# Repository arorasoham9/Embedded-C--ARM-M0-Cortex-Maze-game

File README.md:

# MazeGame

Links to Parts:
Adafruit LIS3DH Triple-Axis Accelerometer (+-2g/4g/8g/16g) : ID 2809 : $4.95 : Adafruit Industries, Unique & fun DIY electronics and kits
Mini Metal Speaker w/ Wires - 8 ohm 0.5W : ID 1890 : $1.95 : Adafruit Industries, Unique & fun DIY electronics and kits

What kinds of internal peripherals will you use? (at least four)
SPI (Screen), I2C (Accelerometer), Timer (Game time), DAC (Game music), GPIO (Buttons)

What kinds of external interface formats will you use? (at least two)
SPI, I2C, GPIO, Analog

Briefly, what are you making and what are you making it out of?
We are going to make a handheld maze game where you control the ball’s movement by rotating the device relative to gravity. The game will be displayed on the MSP2202 TFT LCD Display and angular position will be provided by an LIS3DH triple-axis accelerometer. Tetris music will be played with the MIDI interpreter used in lab via a M2850-8B-0L03R speaker powered by an LM386 audio amplifier. The LM386 is designed for low voltage consumer applications and is adequately powered by a 5 volt supply. The 24AA32AF EEPROM will save the high score even after the device is shut down and restarted. Five tactile push buttons (up/down/left/right/select) will allow the user to navigate any necessary prompts and menus.

Mazes will be dynamically generated. As mazes are completed, they will increase in size and number of rotations required to solve them. A reasonable minimum/maximum rotation limit will be put in place for each size of maze generated.

Briefly, how will you demonstrate it?
We will have the TA play the game. Each maze must be completed within a time limit or the speaker will buzz. The score achieved and the all-time high score will be displayed. The player will be given the choice to start a new game.

Briefly, how will we define the criteria for a successful project? (If your demonstration does not meet these criteria, your score will be negatively affected.)
The rotation based control should track the device’s position accurately and be free of noise/glitches. The game should be able to be played and completed by any adult with no instructions given (any instructions should be easily accessible within the device itself). The maze levels should gradually increase in size as each subsequent maze is completed. The maze size will level off at a point before the maze paths become hard to discern (however we expect people to lose or quit before this point is reached). The player’s score should be a summation of the time left on the countdown for each maze successfully completed. For example, if a certain level has a time limit of 45 seconds, and the player completes the maze in 30 seconds, 15 points will be added to the player’s total score. The high score should be saved and able to be recalled even after the device is shutdown and powered back on. Music should be clearly audible and free of noise.

#CONCLUSION

What did you build? 	
What components (including model numbers) did you use? 	
What challenges did you face, and how did you overcome them? 	
What do you recommend to anyone doing the same thing or using the same components in the future?

We built a maze game that was controlled by rotation of the board. The maze was dynamically generated and increased in size when each level was passed. Players had a set amount of time, which increased as the game continued, to solve each level. Time remaining and current score were displayed on the maze screen. Level score was equal to the amount of time remaining to complete the maze. Menus at start, next level, and end of game were navigated using push buttons and GPIO. After the level or game ended, score was displayed and the player could choose to continue/quit or start a new game. Navigation within the maze was controlled by an accelerometer that interfaced with I2C. EEPROM was used with I2C to save the high score when the game was reset or power was turned off and on. Tetris music played during gameplay and was set up with a MIDI interpreter and DAC output.
The game was displayed on the MSP2202 TFT LCD Display and angular position was provided by an LIS3DH triple-axis accelerometer. 24AA32AF EEPROM allowed our team to save the high score after power cycles. An LM386 amplifier drove a small 0.5 watt M2850-8B-0L03R speaker. Generic 6mm buttons provided the user-input, and LM1117 regulators allowed the team to power the components at their respective voltages.
One major issue that we encountered was related to the randomness of the maze that we were generating. When we initially wrote the maze program we used time.h to seed the random number generator. However, we learned that time.h cannot be used in our microcontroller. After this, we followed the directions on the references site about seeding random with a timer. Our first attempt at this failed and the mazes were still not random. We realized that this was due to the fact that we were calling srand(TIM2->CNT) at the same time each time the game started. In order to fix this we waited for a button to be pressed before we seeded srand, to ensure a different seed each time. 

We also struggled to correctly display colors. We used GIMP to generate the ball, and its output was not displaying colors correctly. We got around this by copying the number of the color we wanted into the array manually. However, the color was lime green against a white background, and the lack of contrast made the ball difficult to view if the player held the maze screen far away.

One final issue we encountered involved music. We used a weak 0.5 W speaker connected to a LM386 amplifier, and getting output at a reasonable volume was difficult. We needed overly complex circuitry to get volume where you didn’t need to place your ear near the speaker to hear. We also struggled with enabling and disabling the music at correct times in the code. When music was stopped and restarted, there was a remaining contribution that interfered with the sound. To fix this, we disabled the timer and set the voices array values to zero before restarting the music. We also did not correctly set the interrupt priority for the music, and the sound clicked as a result. We did not realize this because of the low output of the speaker, but it became clear during the demonstration when we hooked up the output to the lab speakers. If we had tested with the lab speaker, we would likely have been able to fix this issue.

I would recommend a similar project to teams in the future. We ran into many challenges arriving at our final design, however all problems were manageable with proper time management and teamwork. Every component worked well with the exception of the LM386 audio amplifier. We found the LM386 to be very temperamental and prone to noise on our breadboard, and the suggested schematics in the datasheet had to be modified to attain usable results in our case. A small issue we had with the LIS3DH accelerometer was that the datasheet I2C section indicated that a repeated start bit must be sent when the master is receiving data from the accelerometer. We couldn’t figure out how to do this, but after research we found that the repeated start wasn’t necessary- sending a stop bit first followed by a start bit also functioned properly. Once this was figured out the accelerometer worked flawlessly.

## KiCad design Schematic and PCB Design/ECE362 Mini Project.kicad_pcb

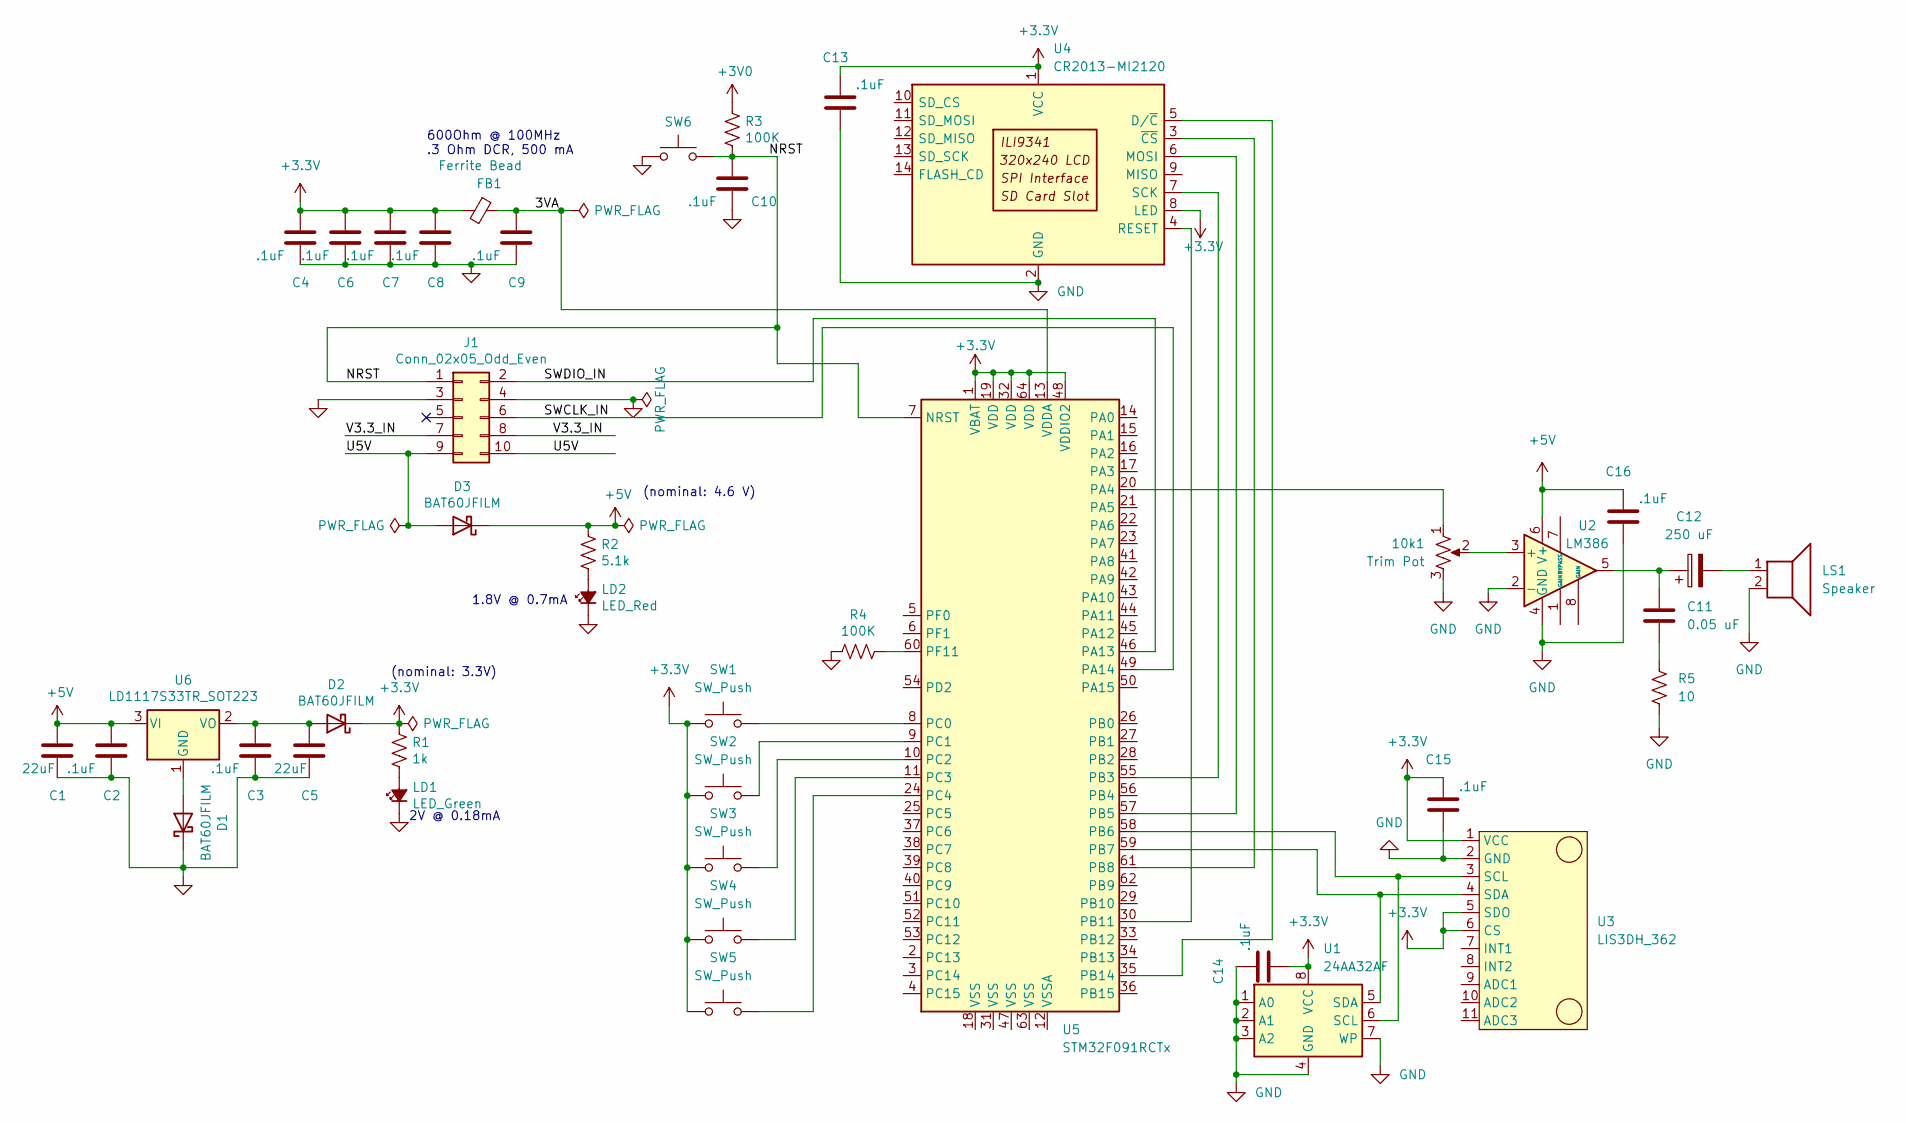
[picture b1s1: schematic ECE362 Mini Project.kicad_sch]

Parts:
10k1: Trim Pot; Potentiometer_Vishay_148-149_Single_Vertical
C1, C5: 22uF; C_0805_2012Metric_Pad1.18x1.45mm_HandSolder
C2, C3, C4, C6, C7, C8, C9, C10, C13, C14, C15, C16: .1uF; C_0805_2012Metric_Pad1.18x1.45mm_HandSolder
C11: 0.05 uF; C_0805_2012Metric_Pad1.18x1.45mm_HandSolder
C12: 250 uF; CP_Radial_D8.0mm_P3.50mm
D1, D2, D3: BAT60JFILM; D_SOD-323
FB1: Ferrite Bead; L_0805_2012Metric_Pad1.15x1.40mm_HandSolder
J1: Conn_02x05_Odd_Even; IDC-Header_2x05_P2.54mm_Vertical
LD1: LED_Green; LED_0805_2012Metric
LD2: LED_Red; LED_0805_2012Metric
LS1: Speaker; SolderWire-0.5sqmm_1x02_P4.6mm_D0.9mm_OD2.1mm
R1: 1k; R_0805_2012Metric_Pad1.20x1.40mm_HandSolder
R2: 5.1k; R_0805_2012Metric_Pad1.20x1.40mm_HandSolder
R3, R4: 100K; R_0805_2012Metric_Pad1.20x1.40mm_HandSolder
R5: 10; R_0805_2012Metric_Pad1.20x1.40mm_HandSolder
SW1, SW2, SW3, SW4, SW5, SW6: SW_Push; SW_PUSH_6mm
U1: 24AA32AF; DIP-8_W7.62mm
U2: LM386; DIP-8_W7.62mm
U3: LIS3DH_362
U4: CR2013-MI2120
U5: STM32F091RCTx; LQFP-64_10x10mm_P0.5mm
U6: LD1117S33TR_SOT223; SOT-223-3_TabPin2

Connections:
+3V0: R3.1
+3V3: C4.1, C6.1, C7.1, C8.1, C13.2, C14.1, C15.2, D2.1 (K), FB1.2, R1.1, SW1.1, SW2.1, SW3.1, SW4.1, SW5.1, U1.8 (VCC), U3.1 (VCC), U3.5 (SDO), U3.6 (CS), U4.1 (VCC), U4.8 (LED), U5.1 (VBAT), U5.19 (VDD), U5.32 (VDD), U5.48 (VDDIO2), U5.64 (VDD)
+5V: C1.1, C2.1, C16.2, D3.1 (K), R2.1, U2.6 (V+), U6.3 (VI)
/3VA: C9.1, FB1.1, U5.13 (VDDA)
/NRST: C10.1, J1.1, R3.2, SW6.2, U5.7 (NRST)
/SWCLK_IN: J1.6, U5.49 (PA14)
/SWDIO_IN: J1.2, U5.46 (PA13)
/U5V: D3.2 (A), J1.9, J1.10
/V3.3_IN: J1.7, J1.8
GND: 10k1.3, C1.2, C2.2, C3.2, C4.2, C5.2, C6.2, C7.2, C8.2, C9.2, C10.2, C13.1, C14.2, C15.1, C16.1, D1.1 (K), J1.3, J1.4, LD1.1 (K), LD2.1 (K), LS1.2, R4.2, R5.2, SW6.1, U1.1 (A0), U1.2 (A1), U1.3 (A2), U1.4 (GND), U1.7 (WP), U2.2 (-), U2.4 (GND), U3.2 (GND), U4.2 (GND)
unnamed: 10k1.2, U2.3 (+)
unnamed: C3.1, C5.1, D2.2 (A), U6.2 (VO)
unnamed: C11.1, C12.1, U2.5
unnamed: C11.2, R5.1
unnamed: D1.2 (A), U6.1 (GND)
unnamed: LD1.2 (A), R1.2
unnamed: LD2.2 (A), R2.2
unnamed: C12.2, LS1.1
unnamed: U1.5 (SDA), U3.4 (SDA), U5.59 (PB7)
unnamed: U4.6 (MOSI), U5.57 (PB5)
unnamed: SW1.2, U5.8 (PC0)
unnamed: SW2.2, U5.9 (PC1)
unnamed: SW3.2, U5.10 (PC2)
unnamed: SW4.2, U5.11 (PC3)
unnamed: 10k1.1, U5.20 (PA4)
unnamed: SW5.2, U5.24 (PC4)
unnamed: U4.4 (RESET), U5.30 (PB11)
unnamed: U4.5 (D/~C), U5.35 (PB14)
unnamed: U4.7 (SCK), U5.55 (PB3)
unnamed: U1.6 (SCL), U3.3 (SCL), U5.58 (PB6)
unnamed: R4.1, U5.60 (PF11)
unnamed: U4.3 (~CS), U5.61 (PB8)

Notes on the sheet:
(nominal: 3.3V)
2V @ 0.18mA
600Ohm @ 100MHz .3 Ohm DCR, 500 mA
1.8V @ 0.7mA
(nominal: 4.6 V)

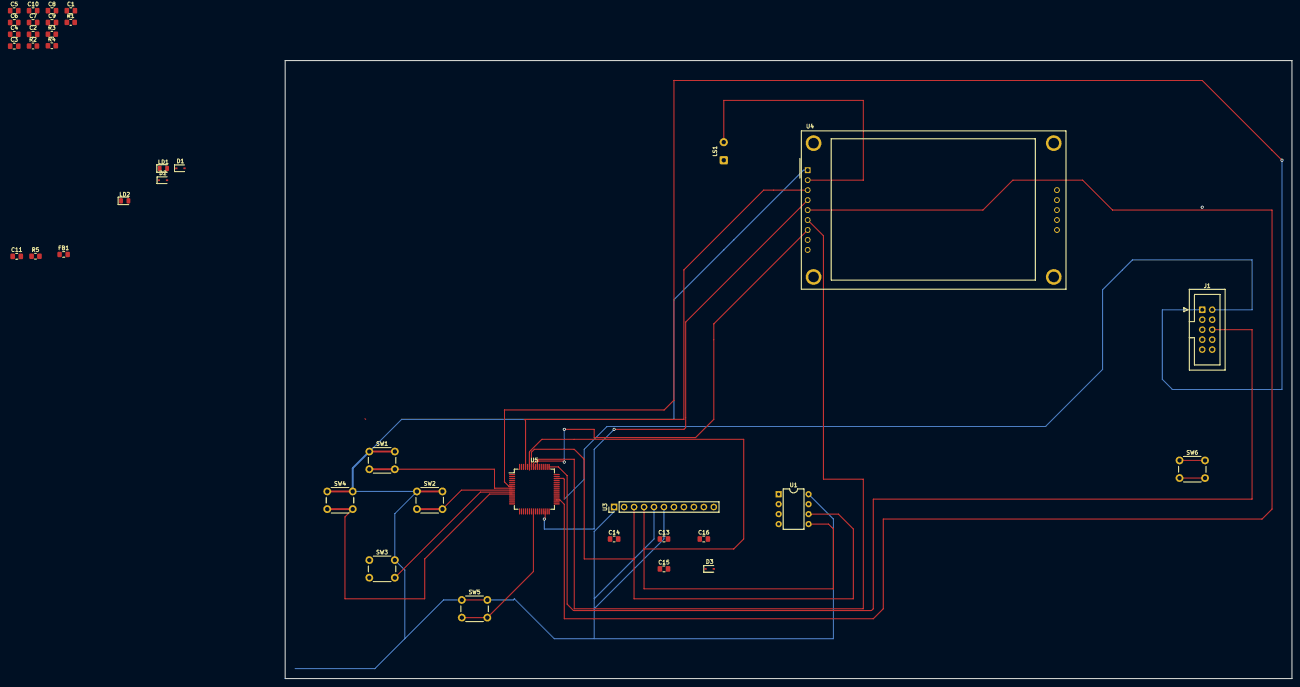
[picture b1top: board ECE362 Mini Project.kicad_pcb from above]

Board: 2 copper layers, 256.5 x 157.5 mm, 39 parts (1 on the bottom side), 27 nets.

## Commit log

2022-05-16 Final Commit
2022-05-16 Final Design and Code
